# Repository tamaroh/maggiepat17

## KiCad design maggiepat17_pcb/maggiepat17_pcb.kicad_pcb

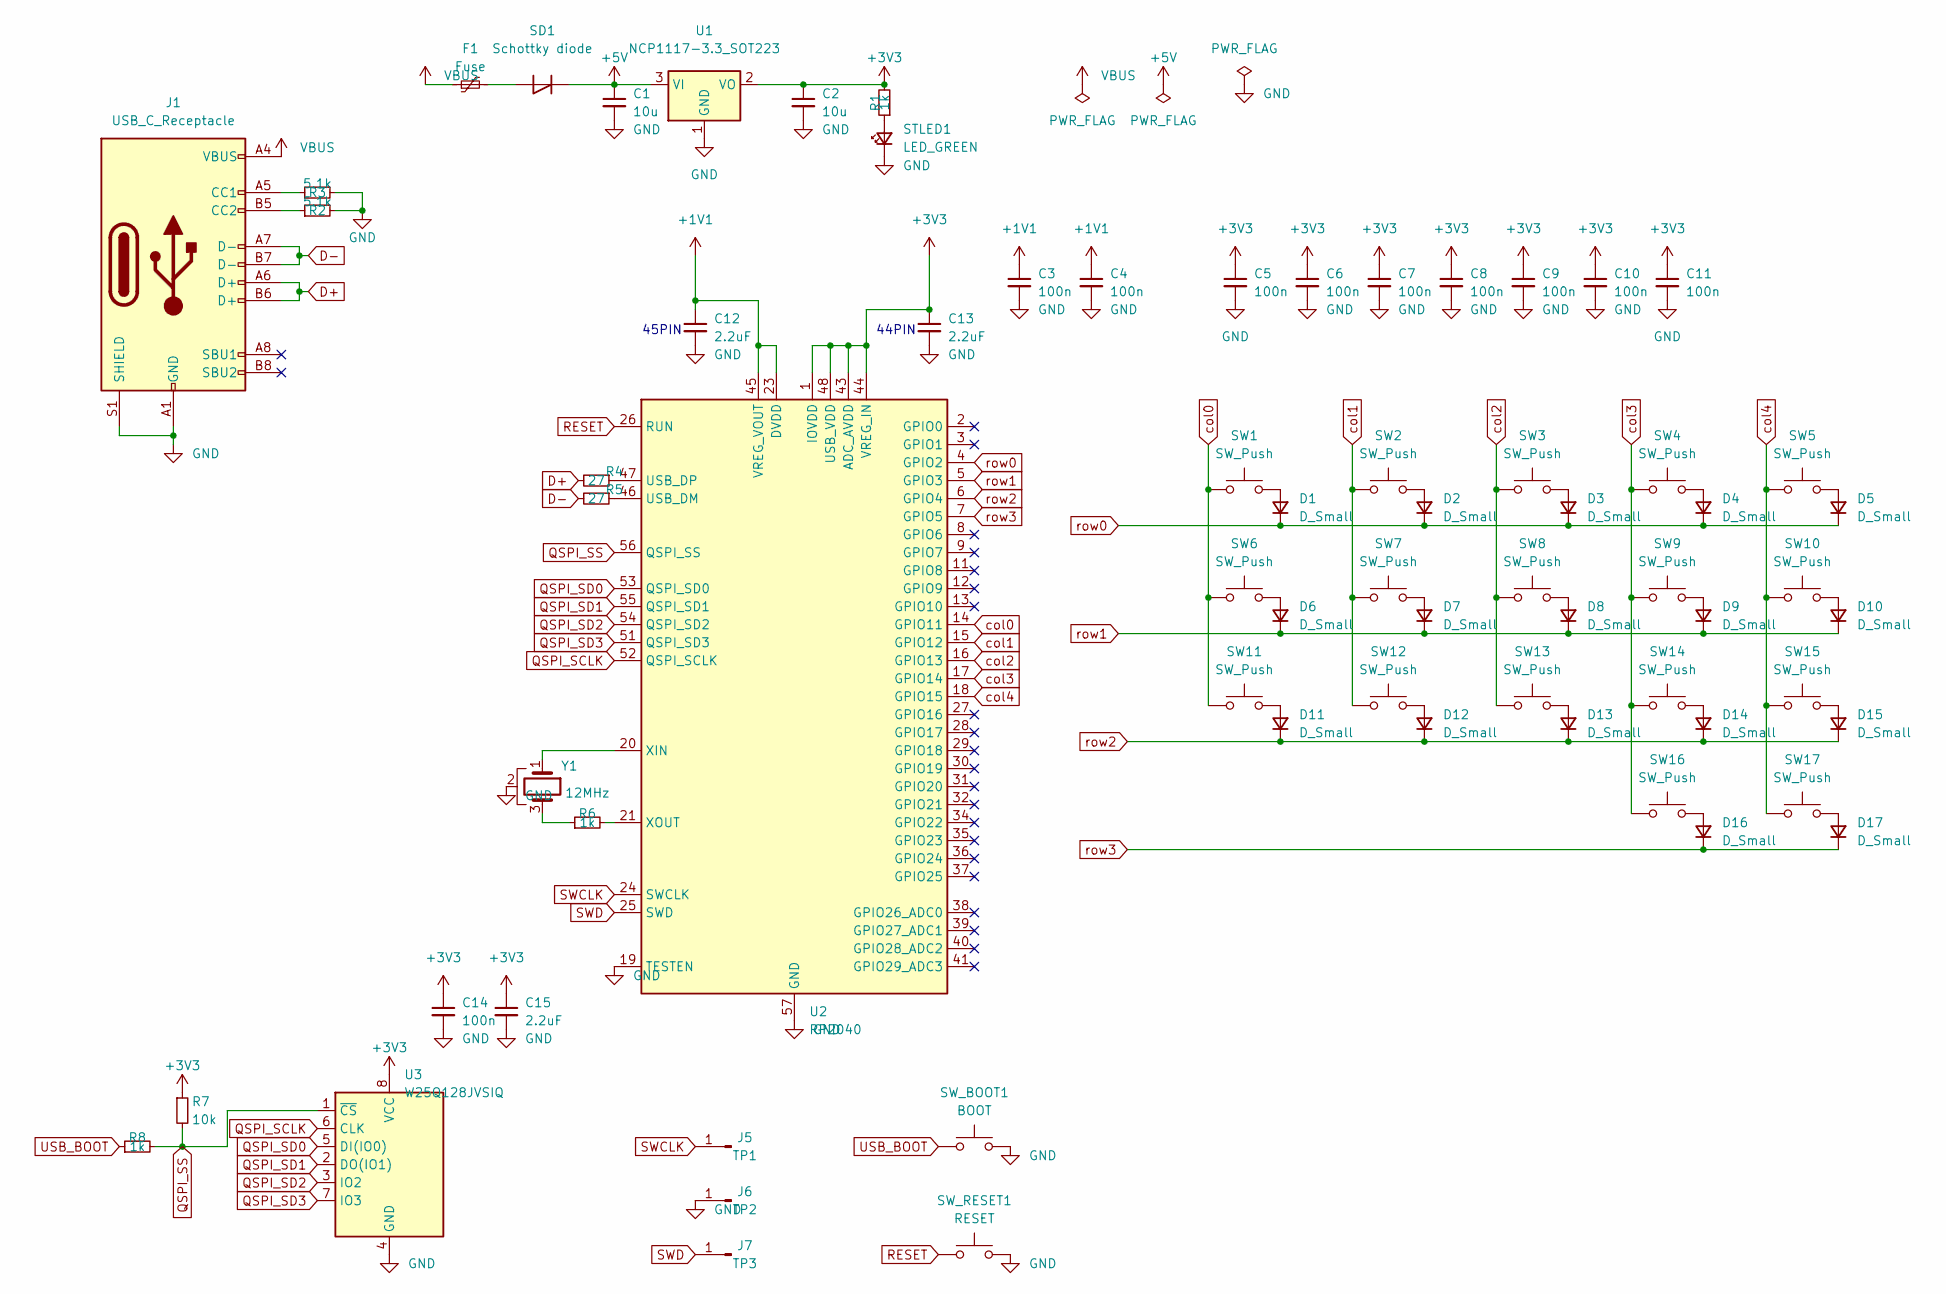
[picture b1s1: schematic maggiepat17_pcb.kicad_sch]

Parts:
C1, C2: 10u; C_1206_3216Metric
C3, C4, C5, C6, C7, C8, C9, C10, C11, C14: 100n; C_0402_1005Metric
C12, C13, C15: 2.2uF; C_0402_1005Metric
D1, D2, D3, D4, D5, D6, D7, D8, D9, D10, D11, D12, D13, D14, D15, D16, D17: D_Small; D_SOD-123
F1: Fuse; Fuse_0603_1608Metric; LCSC C122965
J1: USB_C_Receptacle; USB_C_Receptacle_HRO_TYPE-C-31-M-12
J5: TP1; TestPoint_Pad_D1.0mm
J6: TP2; TestPoint_Pad_D1.0mm
J7: TP3; TestPoint_Pad_D1.0mm
R1, R6, R8: 1k; R_0402_1005Metric
R2, R3: 5.1k; R_0402_1005Metric
R4, R5: 27; R_0402_1005Metric
R7: 10k; R_0402_1005Metric
SD1: Schottky diode; D_SOD-123
STLED1: LED_GREEN; LED_0402_1005Metric
SW1, SW2, SW3, SW4, SW5, SW6, SW7, SW8, SW9, SW10, SW11, SW12, SW13, SW14, SW15, SW16, SW17: SW_Push; keyswitch_cherrymx_hotswap_1u
SW_BOOT1: BOOT; SW_SPST_PTS810
SW_RESET1: RESET; SW_SPST_PTS810
U1: NCP1117-3.3_SOT223; SOT-223-3_TabPin2
U2: RP2040; QFN-56-1EP_7x7mm_P0.4mm_EP3.2x3.2mm
U3: W25Q128JVSIQ; SOIC-8_5.23x5.23mm_P1.27mm
Y1: 12MHz; Resonator_SMD_Murata_CSTxExxV-3Pin_3.0x1.1mm

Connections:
+1V1: C3.1, C4.1, C12.1, U2.23 (DVDD), U2.45 (VREG_VOUT), U2.50 (DVDD)
+3V3: C2.1, C5.1, C6.1, C7.1, C8.1, C9.1, C10.1, C11.1, C13.1, C14.1, C15.1, R1.2, R7.1, U1.2 (VO), U2.1 (IOVDD), U2.10 (IOVDD), U2.22 (IOVDD), U2.33 (IOVDD), U2.42 (IOVDD), U2.43 (ADC_AVDD), U2.44 (VREG_IN), U2.48 (USB_VDD), U2.49 (IOVDD), U3.8 (VCC)
+5V: C1.1, SD1.1 (K), U1.3 (VI)
D+: J1.A6 (D+), J1.B6 (D+), R4.2
D-: J1.A7 (D-), J1.B7 (D-), R5.2
GND: C1.2, C2.2, C3.2, C4.2, C5.2, C6.2, C7.2, C8.2, C9.2, C10.2, C11.2, C12.2, C13.2, C14.2, C15.2, J1.A1 (GND), J1.A12 (GND), J1.B1 (GND), J1.B12 (GND), J1.S1 (SHIELD), J6.1, R2.2, R3.2, STLED1.1 (K), SW_BOOT1.2, SW_RESET1.2, U1.1 (GND), U2.19 (TESTEN), U2.57 (GND), U3.4 (GND), Y1.2
unnamed: D1.2 (A), SW1.2
unnamed: D2.2 (A), SW2.2
unnamed: D3.2 (A), SW3.2
unnamed: D4.2 (A), SW4.2
unnamed: D5.2 (A), SW5.2
unnamed: D6.2 (A), SW6.2
unnamed: D7.2 (A), SW7.2
unnamed: D8.2 (A), SW8.2
unnamed: D9.2 (A), SW9.2
unnamed: D10.2 (A), SW10.2
unnamed: D11.2 (A), SW11.2
unnamed: D12.2 (A), SW12.2
unnamed: D13.2 (A), SW13.2
unnamed: D14.2 (A), SW14.2
unnamed: D15.2 (A), SW15.2
unnamed: D16.2 (A), SW16.2
unnamed: D17.2 (A), SW17.2
unnamed: J1.A5 (CC1), R3.1
unnamed: J1.B5 (CC2), R2.1
unnamed: R6.1, Y1.3
unnamed: F1.2, SD1.2 (A)
unnamed: R1.1, STLED1.2 (A)
unnamed: R5.1, U2.46 (USB_DM)
unnamed: R4.1, U2.47 (USB_DP)
unnamed: U2.20 (XIN), Y1.1
unnamed: R6.2, U2.21 (XOUT)
QSPI_SCLK: U2.52 (QSPI_SCLK), U3.6 (CLK)
QSPI_SD0: U2.53 (QSPI_SD0), U3.5 (DI(IO0))
QSPI_SD1: U2.55 (QSPI_SD1), U3.2 (DO(IO1))
QSPI_SD2: U2.54 (QSPI_SD2), U3.3 (IO2)
QSPI_SD3: U2.51 (QSPI_SD3), U3.7 (IO3)
QSPI_SS: R7.2, R8.2, U2.56 (QSPI_SS), U3.1 (~CS)
RESET: SW_RESET1.1, U2.26 (RUN)
SWCLK: J5.1, U2.24 (SWCLK)
SWD: J7.1, U2.25 (SWD)
USB_BOOT: R8.1, SW_BOOT1.1
VBUS: F1.1, J1.A4 (VBUS), J1.A9 (VBUS), J1.B4 (VBUS), J1.B9 (VBUS)
col0: SW1.1, SW6.1, SW11.1, U2.14 (GPIO11)
col1: SW2.1, SW7.1, SW12.1, U2.15 (GPIO12)
col2: SW3.1, SW8.1, SW13.1, U2.16 (GPIO13)
col3: SW4.1, SW9.1, SW14.1, SW16.1, U2.17 (GPIO14)
col4: SW5.1, SW10.1, SW15.1, SW17.1, U2.18 (GPIO15)
row0: D1.1 (K), D2.1 (K), D3.1 (K), D4.1 (K), D5.1 (K), U2.4 (GPIO2)
row1: D6.1 (K), D7.1 (K), D8.1 (K), D9.1 (K), D10.1 (K), U2.5 (GPIO3)
row2: D11.1 (K), D12.1 (K), D13.1 (K), D14.1 (K), D15.1 (K), U2.6 (GPIO4)
row3: D16.1 (K), D17.1 (K), U2.7 (GPIO5)

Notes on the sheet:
45PIN
44PIN

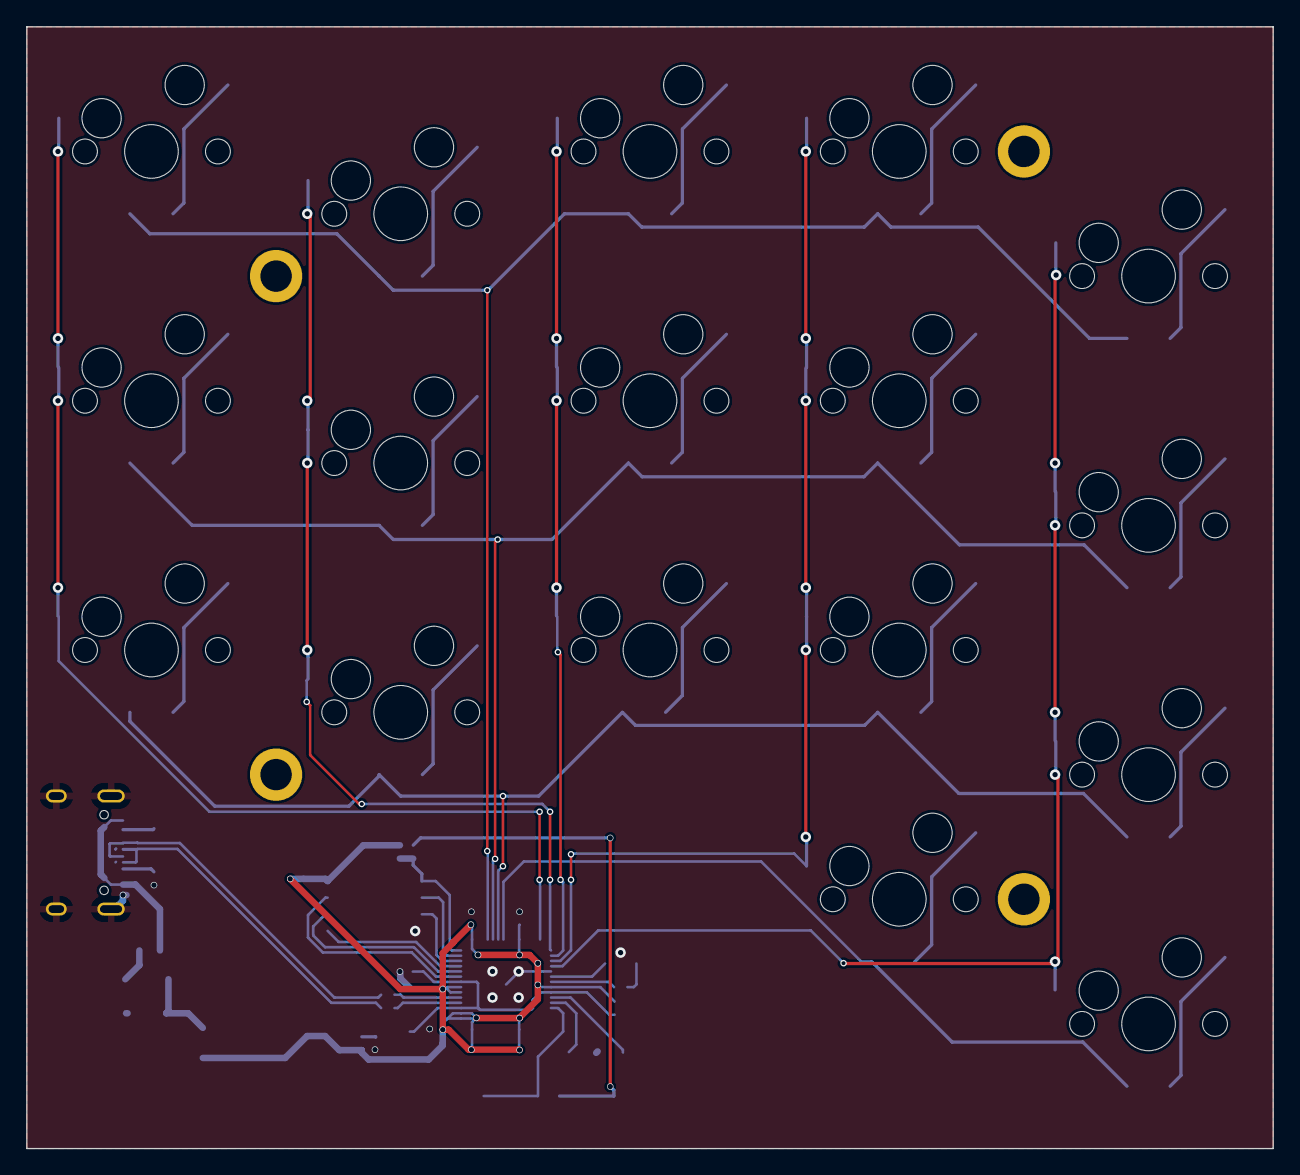
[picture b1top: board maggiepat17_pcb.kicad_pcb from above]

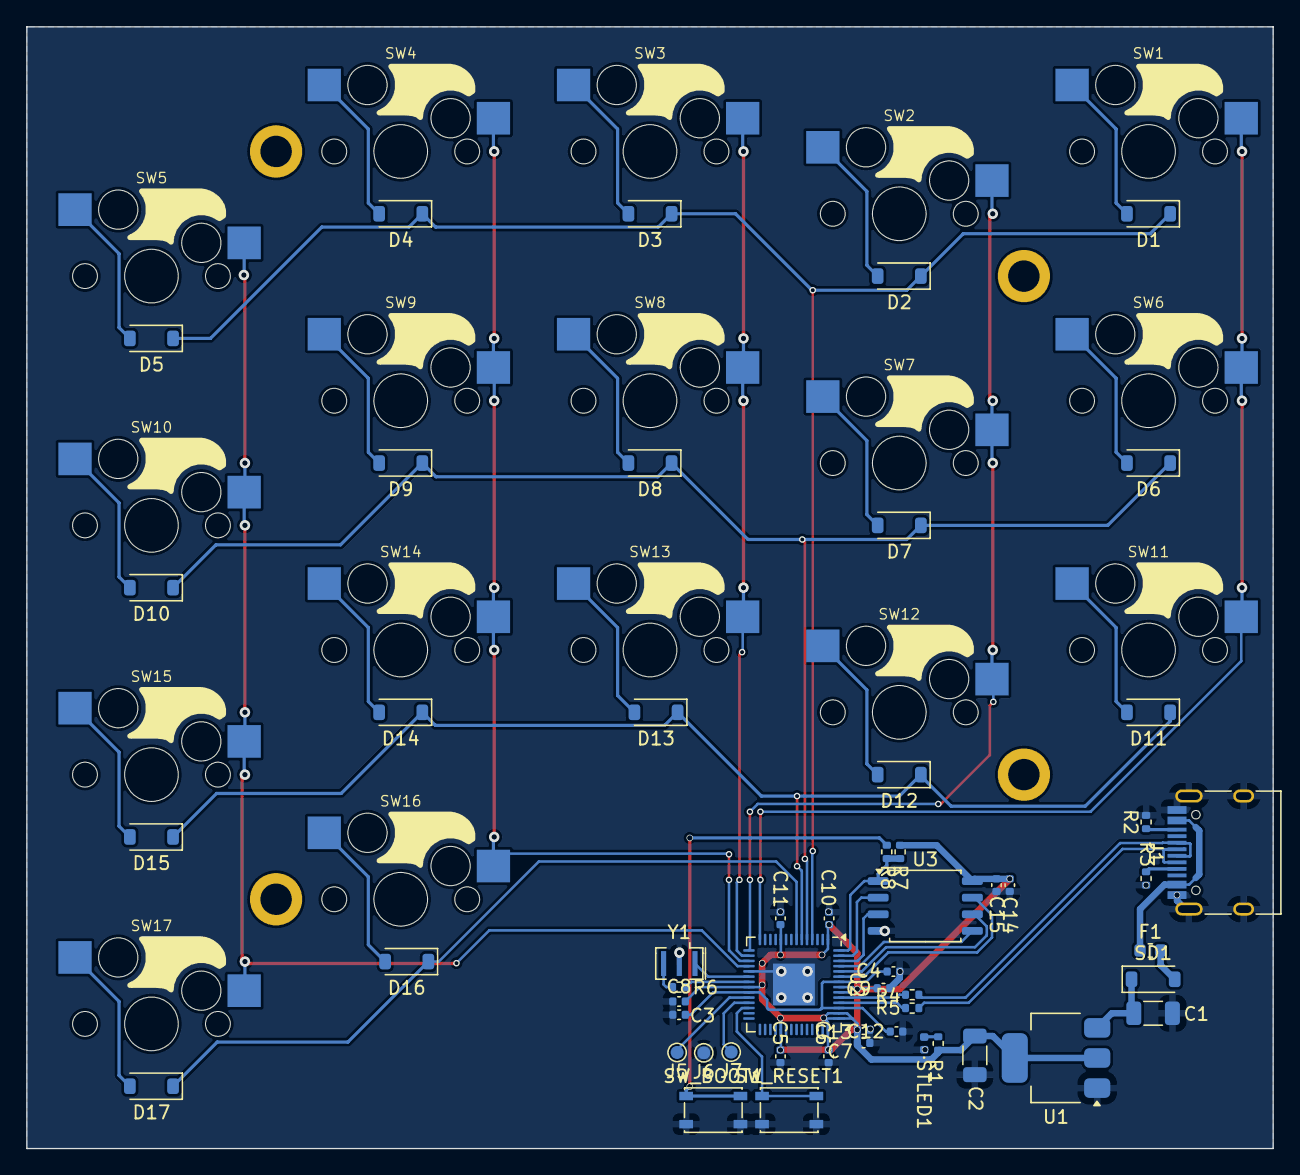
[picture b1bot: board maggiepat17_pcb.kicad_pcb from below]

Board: 2 copper layers, 95.2 x 85.7 mm, 70 parts (70 on the bottom side), 52 nets.

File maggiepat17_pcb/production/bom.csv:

Designator,Footprint,Quantity,Value,LCSC Part #
"C1, C2",1206,2,10u,C77090
"C10, C11, C14, C3, C4, C5, C6, C7, C8, C9",0402,10,100n,C1525
"C12, C13, C15",0402,3,2.2uF,C307418
"D1, D10, D11, D12, D13, D14, D15, D16, D17, D2, D3, D4, D5, D6, D7, D8, D9",D_SOD-123,17,D_Small,C109203
F1,0603,1,Fuse,C122965
J1,USB_C_Receptacle_HRO_TYPE-C-31-M-12,1,USB_C_Receptacle,C165948
"R1, R6, R8",0402,3,1k,C11702
"R2, R3",0402,2,5.1k,C25905
"R4, R5",0402,2,27,C25100
R7,0402,1,10k,C25744
SD1,D_SOD-123,1,Schottky diode,C8598
STLED1,0402,1,LED_GREEN,C130723
SW_BOOT1,SW_SPST_PTS810,1,BOOT,C92589
SW_RESET1,SW_SPST_PTS810,1,RESET,C92589
U1,SOT-223-3_TabPin2,1,NCP1117-3.3_SOT223,C347222
U2,QFN-56-1EP_7x7mm_P0.4mm_EP3.2x3.2mm,1,RP2040,C2040
U3,SOIC-8_5.23x5.23mm_P1.27mm,1,W25Q128JVSIQ,C190862
Y1,Resonator_SMD_Murata_CSTxExxV-3Pin_3.0x1.1mm,1,12MHz,C341520

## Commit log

2024-07-03 added switches
2024-07-03 changed USB connector
2024-07-03 fixed switch metrix
2024-07-21 created PCBA order files, need to replace
2024-07-21 replaced LCSC part #, still need to fix
2024-08-13 updated bom files, order passed
2024-11-02 added firmware, via.json
